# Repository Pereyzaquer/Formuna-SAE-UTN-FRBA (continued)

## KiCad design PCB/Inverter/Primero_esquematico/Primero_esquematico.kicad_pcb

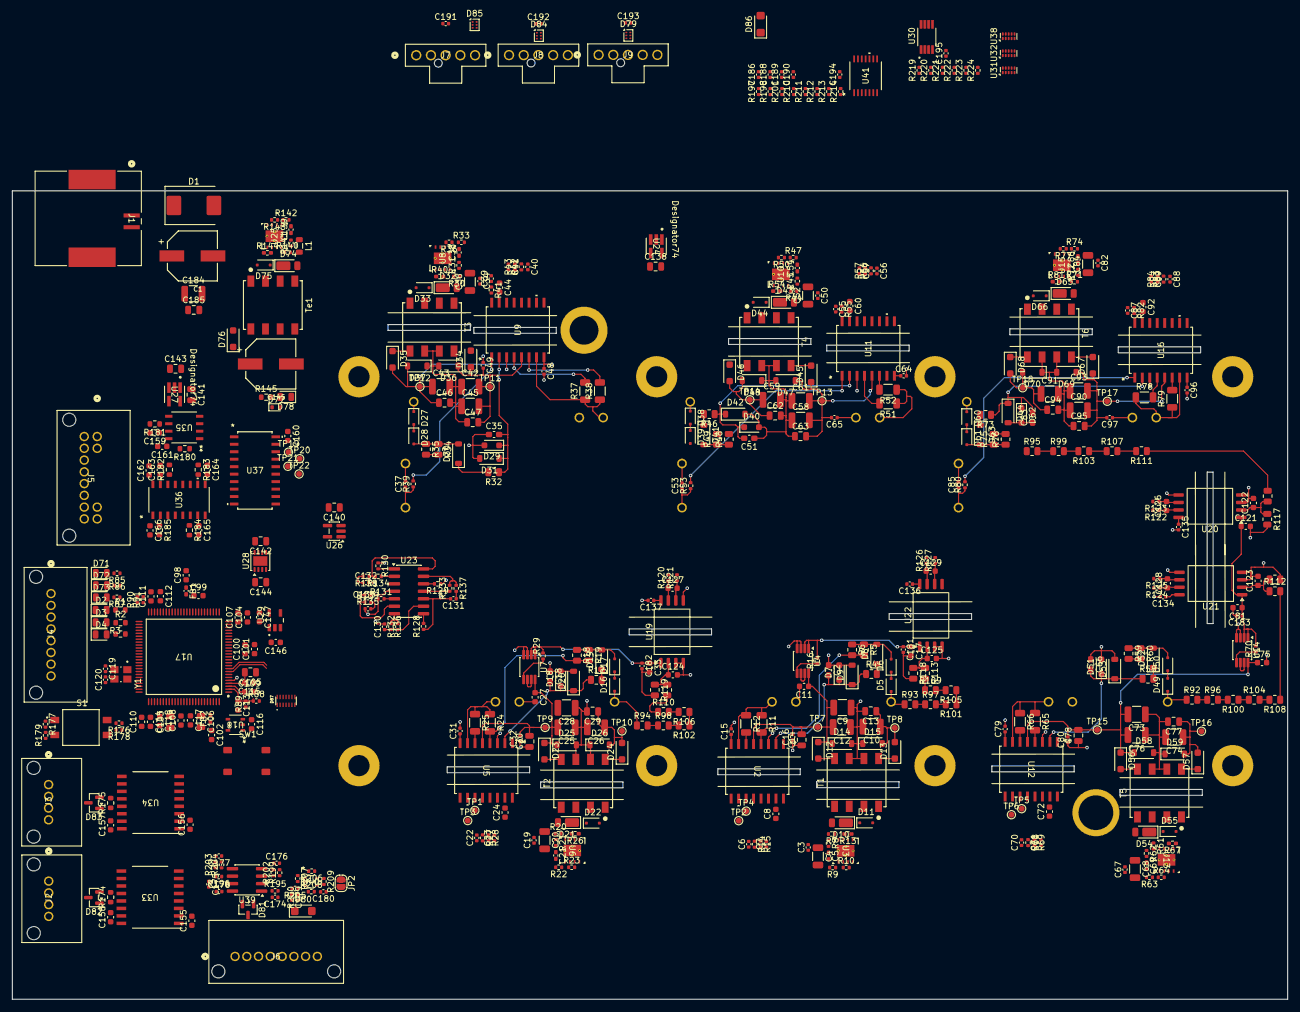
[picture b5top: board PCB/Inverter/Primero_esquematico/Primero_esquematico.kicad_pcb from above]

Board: 6 copper layers, 216.8 x 137.4 mm, 536 parts (1 on the bottom side), 303 nets.

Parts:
C1, C145: 220uF; WCAP-PSLC_8X11.7_DXL_
C2, C18, C35, C51, C66, C83: 56pF; C_0603_1608Metric_Pad1.08x0.95mm_HandSolder
C3, C15, C16, C19, C31, C32, C34, C48, C49, C50, C64, C65, C67, C79, C80, C82, C96, C97, C134, C135, C136, C137, C178, C180, C181, C182, C183, C186, C188, C189, C190: 100nF; C_0402_1005Metric
C4, C20, C36, C52, C68, C84: 10 uF; C_1206_3216Metric
C5, C21, C38, C54, C69, C86, C139: 47nF; C_0402_1005Metric_Pad0.74x0.62mm_HandSolder
C6, C7, C22, C23, C40, C41, C56, C57, C70, C71, C88, C89: 100pF; C_0402_1005Metric
C8, C24, C44, C60, C72, C92, C121: 1uF; C_0603_1608Metric
C9, C12, C25, C28, C42, C45, C58, C61, C73, C76, C90, C93: 10uF; C_1210_3225Metric
C10, C26, C43, C59, C74, C91, C184: 22uF; C_1210_3225Metric
C11, C17, C27, C33, C75, C81: 4.8uF; C_0603_1608Metric
C13, C14, C29, C30, C46, C47, C62, C63, C77, C78, C94, C95, C140, C142, C143, C144: 1uF; C_0805_2012Metric
C37, C53, C85, C119, C120: 10pF; C_0402_1005Metric
C39, C55, C87: 220nF; C_0402_1005Metric
C98, C99, C100, C101, C104, C107: 2.2uF; C_0603_1608Metric
C102: 10uF; C_0603_1608Metric
C103, C105, C106, C138, C141: 10uF; C_0805_2012Metric
C108, C109, C110, C111, C112, C113, C114, C115, C116, C117, C118, C155, C156, C157, C158, C160, C161, C162: 100nF; C_0603_1608Metric
C122, C123, C124, C125, C126, C127, C128, C129: 1nF; C_0603_1608Metric
C130, C131, C132, C133, C174, C175, C195: 1nF; C_0402_1005Metric
C146, C147: 0,1uF; C_0603_1608Metric
C159, C163, C164, C165, C166: 10nF; C_0603_1608Metric
C176, C177, C179: 2.2nF; C_0402_1005Metric
C185: 100nF; C_0805_2012Metric
C191, C192, C193: 47nF; C_0402_1005Metric
C194: 1uF; C_0402_1005Metric
D1: SMDJ13A; D_SMC
D2, D3, D4, D71, D72, D73, D78: APT2012EC; LED_0805_2012Metric
D5, D6, D16, D17, D27, D28, D38, D39, D49, D50, D60, D61: STTH112A; D_SOD-323F
D7, D18, D29, D40, D51, D62: BAT54WS-7-F; D_SOD-323_HandSoldering
D8, D19, D30, D41, D52, D63: BZT52C2V7-TP; D_SOD-123
D9, D20, D31, D42, D53, D64: MMSZ5242B-7-F; D_SOD-123
D10, D21, D32, D43, D54, D65, D74: DFLZ24Q-7; D_PowerDI-123
D11, D22, D33, D44, D55, D66, D75: 1N4148WS-Q; D_SOD-323F
D12, D13, D23, D24, D34, D35, D45, D46, D56, D57, D67, D68, D76: SDM1U100S1F-7; D_SOD-123F
D14, D25, D36, D47, D58, D69: BZT52C18-7-F; D_SOD-123
D15, D26, D37, D48, D59, D70: BZT52B8V2-E3-08; D_SOD-123
D77: SZMM5Z5V6T1G; D_SOD-523
D79, D84, D85: PESD3V3L4UF; SOT-886
D80, D86: SMF16A; D_SMF
D81, D82, D83: PESD5V0S2UAT,215; SOT-23
D87: TPD6E05U06RVZR; SON50P135X350X55-14N
FB1: 60 Ohm; L_0402_1005Metric_Pad0.77x0.64mm_HandSolder
FB2: 220 Ohms; L_0402_1005Metric_Pad0.77x0.64mm_HandSolder
J1: 349128022; CONN_SD-34912-001_02_MOL
J2, J3: 347920040; CONN04_34792_MOL
J4, J6: 347928082; CONN08_34792_MOL
J5: 348250125; CONN_SD-34825-001_12_MOL
J7, J8, J9: 1053091205; CONN_SD-105309-100_05_MOL
JP2: solotest; SolderJumper-2_P1.3mm_Open_RoundedPad1.0x1.5mm
L1: MLZ2012N6R8LT000; L_0805_2012Metric
R1, R2, R3: 2k2; R_0603_1608Metric
R4, R17, R32, R46, R58, R73: 475; R_0805_2012Metric
R5, R6, R18, R19, R34, R35, R48, R49, R59, R60, R75, R76: 2k; R_0805_2012Metric
R7, R20, R30, R44, R61, R71, R140: 246k; R_0402_1005Metric
R8, R21, R31, R45, R62, R72, R141: 37k; R_0402_1005Metric
R9, R22, R33, R47, R63, R74, R142: 12k1; R_0402_1005Metric
R10, R23, R36, R50, R64, R77, R143: 110k; R_0402_1005Metric
R11, R24, R37, R51, R65, R78: 2.4; R_1206_3216Metric
R12, R25, R38, R52, R66, R79: 5.1; R_1206_3216Metric
R13, R26, R40, R54, R67, R81: 154k; R_0402_1005Metric_Pad0.72x0.64mm_HandSolder
R14, R27, R42, R56, R68, R83, R220, R224: 5k; R_0402_1005Metric
R15, R28, R43, R57, R69, R84: 2k; R_0402_1005Metric
R16, R29, R70: 330k; R_0402_1005Metric
R39, R53, R80: 10; R_0402_1005Metric
R41, R55, R82: 360; R_0402_1005Metric
R85, R86, R87: 1k5; R_0402_1005Metric
R88, R90, R91, R177, R179: 0; R_0402_1005Metric
R89, R176, R178, R210, R211, R212, R213, R223: 10k; R_0402_1005Metric
R92, R93, R94, R95, R96, R97, R98, R99, R100, R101, R102, R103, R104, R105, R106, R107, R108, R109, R110, R111, R112, R113, R114, R115: 100k; R_0805_2012Metric
R116, R117, R118, R119: 2k2; R_0805_2012Metric
R120, R121, R122, R123, R124, R125, R126, R127: 4k42; R_0402_1005Metric
R128, R129, R130, R131, R132, R133, R134, R135: 7k68; R_0402_1005Metric
R136, R137, R138, R139, R195, R196: 100; R_0402_1005Metric
R144: 158k; R_0402_1005Metric_Pad0.72x0.64mm_HandSolder
R145: 1k5; R_0603_1608Metric
R174, R175, R181, R182, R183, R184, R185: 120; R_0603_1608Metric
R180: 10k; R_0603_1608Metric
R197, R198, R201: 820; R_0402_1005Metric
R199, R200, R203: 220k; R_0402_1005Metric
R202, R204, R205: 470k; R_0402_1005Metric
R206: 62k; R_0402_1005Metric
R207: 47k; R_0402_1005Metric
R208: 100k; R_0402_1005Metric
R209, R214: 1k; R_0402_1005Metric
R219: 39; R_0402_1005Metric
R221: 20k; R_0402_1005Metric
R222: 11k; R_0402_1005Metric
S1: DS04-254-2-02BK-SMT-TR; SW_DS04-254-2-02BK-SMT-TR
SW1: IT-1187-160GM-G
T1, T2, T3, T4, T5, T6: 750317595; WE-FLYTI_EP7_4436
TP1, TP2, TP3, TP4, TP5, TP6, TP7, TP8, TP9, TP10, TP11, TP12, TP13, TP14, TP15, TP16, TP17, TP18, TP19, TP20, TP21, TP22: TestPoint; TestPoint_Pad_D1.0mm
Te1: Trafo 30uH - 3:1; WE-FLYTI_EP7_4436
U1: FS950R08A6P2BBPSA1; IC_FS950R08A6P2BBPSA1
U2, U5, U9, U11, U12, U16: UCC21750QDWRQ1; SOIC16_DW_TEX-L
U3, U6, U8, U10, U13, U15, U25: LM25180QNGURQ1; NGU0008C
U4, U7, U14: LP2951-5.0_VSSOP; VSSOP-8_3x3mm_P0.65mm
U17: F280049CPZS; PZ0100A_L
U18: TPS3823-33DBVR; DBV5-L
U19, U20, U21, U22: AMC1311BQDWVRQ1; SOIC-8_7.5x5.85mm_P1.27mm
U23: TLV9004QDRQ1; SOIC-14_3.9x8.7mm_P1.27mm
U24, U27: TPS7A2050PDBVR; DBV0005A-IPC_A
U26: LP5907QMFX-3.3Q1; SC-74A-5_1.55x2.9mm_P0.95mm
U28: TLV76733QWDRBRQ1; VSON-8-1EP_3x3mm_P0.65mm_EP1.65x2.4mm
U29: REF2030-Q1; SOT95P0280X110-5N
U30: TLV1702AQDGKRQ1; SOP65P490X110-8N
U31, U32, U38: TPD4E05U06DQA; USON-10_2.5x1.0mm_P0.5mm
U33, U34: ISO1042DWR; DW0016B_HV
U35: SN65HVD82DR; D8_TEX-L
U36: AM26LS32AIDR; D16-L
U37: SN74LVC245ANSR; NS20-L
U39: OPA2196xD; SOIC-8_3.9x4.9mm_P1.27mm
U40: TLV1701AQDCKRQ1; SOIC_DCKRQ1_TEX-L
U41: OPA4991QPWRQ1; TSSOP_PWRQ1_TEX-L
Y1: ABM8GAIG-20.000MHZ-8-7Z-T3; XTAL_ABM8GAIG-20.000MHZ-8-7Z-T3

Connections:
+1V5: R214.1, U29.1 (VBIAS)
+3.3V_analog: C134.1, C135.1, C136.1, C137.1, C140.2, C178.2, C186.2, C191.1, C192.1, C193.1, D79.1 (K1), D84.1 (K1), D85.1 (K1), J7.1, J8.1, J9.1, JP2.1 (A), R206.1, R209.1, R213.1, R224.1, U19.8 (VDD2), U20.8 (VDD2), U21.8 (VDD2), U22.8 (VDD2), U23.3 (V+), U26.5 (OUT), U30.8 (VCC), U39.8 (V+), U40.5 (V+), U41.4 (V+)
+3.3_digital: C8.2, C24.2, C44.2, C60.2, C72.2, C92.2, C98.1, C102.1, C116.1, C144.2, C155.1, C156.1, C160.1, D87.14 (D1P), FB1.1, FB2.1, J4.1, R1.2, R2.2, R3.2, R14.2, R15.2, R27.2, R28.2, R42.2, R43.2, R56.2, R57.2, R68.2, R69.2, R83.2, R84.2, R89.1, R176.1, R178.1, U2.15 (VCC), U5.15 (VCC), U9.15 (VCC), U11.15 (VCC), U12.15 (VCC), U16.15 (VCC), U18.3 (*MR), U18.5 (VDD), U28.1 (OUT), U28.3 (SNS), U33.1 (VCC1), U34.1 (VCC1), U37.1 (DIR), U37.20 (VCC)
+3V0: C104.1, C107.1, C147.1, R220.1, R222.1, U17.24 (VREFHIB_VREFHIC), U17.25 (VREFHIA), U29.5 (VREF)
+5V_Can_1: C158.1, J2.4, U33.11 (VCC2), U33.16 (VCC2)
+5V_Can_2: C157.1, J3.4, U34.11 (VCC2), U34.16 (VCC2)
+5V_analog: C138.2, D86.1 (A1), J6.1, J6.2, U24.5 (OUT)
+5V_digital: C141.2, C146.1, C161.1, C162.1, J5.5, R180.2, U27.5 (OUT), U29.3 (EN), U29.4 (VIN), U32.4 (D2+), U32.5 (D2-), U35.8 (VCC), U36.4 (G), U36.16 (VCC)
+12V: C1.1, C3.2, C4.1, C19.2, C20.1, C34.2, C36.1, C50.2, C52.1, C67.2, C68.1, C82.2, C84.1, C184.1, C185.1, D1.1 (A1), D10.2 (A), D21.2 (A), D32.2 (A), D43.2 (A), D54.2 (A), D65.2 (A), J1.1, L1.1, R7.1, R20.1, R30.1, R44.1, R61.1, R71.1, T1.4, T2.4, T3.4, T4.4, T5.4, T6.4, U3.3 (VIN), U6.3 (VIN), U8.3 (VIN), U10.3 (VIN), U13.3 (VIN), U15.3 (VIN)
/pcb_logica/A: TP19.1 (1_1), U17.93 (GPIO10), U37.18 (B1)
/pcb_logica/B: TP20.1 (1_1), U17.52 (GPIO11), U37.17 (B2)
/pcb_logica/Boot_Mode_1: R178.2, S1.2B, U17.64 (GPIO32)
/pcb_logica/Boot_Mode_2: R176.2, S1.1B, U17.56 (GPIO24)
/pcb_logica/CAN_RX_A: U17.98 (GPIO30), U33.5 (RXD)
/pcb_logica/CAN_RX_B: U17.50 (GPIO13), U34.5 (RXD)
/pcb_logica/CAN_TX_A: U17.99 (GPIO31), U33.3 (TXD)
/pcb_logica/CAN_TX_B: U17.51 (GPIO12), U34.3 (TXD)
/pcb_logica/Clk: U17.74 (GPIO08), U35.4 (D)
/pcb_logica/Current_A: C190.1, R201.2, U17.23 (A0_B15_C15_DACA_OUT)
/pcb_logica/Current_B: C189.1, R198.2, U17.41 (B0)
/pcb_logica/Current_C: C188.1, R197.2, U17.19 (C0)
/pcb_logica/Data: TP22.1 (1_1), U17.84 (GPIO07), U37.15 (B4)
/pcb_logica/ErrorDC: R91.2, R224.2, U30.1 (1OUT), U30.7 (2OUT)
/pcb_logica/F280049C/GPIO18_X2: C119.1, U17.68 (GPIO18_X2), Y1.1
/pcb_logica/F280049C/GP_25_LED_A: R85.1, U17.57 (GPIO25)
/pcb_logica/F280049C/GP_26_LED_B: R86.1, U17.58 (GPIO26)
/pcb_logica/F280049C/GP_27_LED_C: R87.1, U17.59 (GPIO27)
/pcb_logica/F280049C/GP_59_WD: U17.92 (GPIO59), U18.4 (WDI)
/pcb_logica/F280049C/X1: C120.1, U17.69 (X1), Y1.3
/pcb_logica/GD_FLT: C7.2, C23.2, C41.2, C57.2, C71.2, C89.2, D2.2 (A), R1.1, R15.1, R28.1, R43.1, R57.1, R69.1, R84.1, U2.13 (*FLT), U5.13 (*FLT), U9.13 (*FLT), U11.13 (*FLT), U12.13 (*FLT), U16.13 (*FLT), U17.65 (GPIO56)
/pcb_logica/GD_RDY: C6.2, C22.2, C40.2, C56.2, C70.2, C88.2, D3.2 (A), R2.1, R14.1, R27.1, R42.1, R56.1, R68.1, R83.1, U2.12 (RDY), U5.12 (RDY), U9.12 (RDY), U11.12 (RDY), U12.12 (RDY), U16.12 (RDY), U17.66 (GPIO57)
/pcb_logica/LogicSupply/5V_FB: C142.2, C143.2, C145.1, D76.1 (K), D77.1 (K), R145.1, U24.1 (IN), U24.3 (EN), U26.1 (IN), U26.3 (EN), U27.1 (IN), U27.3 (EN), U28.5 (EN), U28.8 (IN)
/pcb_logica/Mcu_reset: C113.1, D87.13 (D1N), J4.2, R88.1, R89.2, U17.2 (XRS_N), U18.1 (*RESET)
/pcb_logica/OCD_OUT: D79.6 (K4), D84.6 (K4), D85.6 (K4), J7.5, J8.5, J9.5, R90.2, R213.2
/pcb_logica/PWM_H_A: TP6.1 (1_1), U12.10 (IN+), U16.11 (IN), U17.79 (GPIO00)
/pcb_logica/PWM_H_B: TP2.1 (1_1), U2.10 (IN+), U17.77 (GPIO02)
/pcb_logica/PWM_H_C: TP3.1 (1_1), U5.10 (IN+), U9.11 (IN), U11.11 (IN), U17.75 (GPIO04)
/pcb_logica/PWM_L_A: TP5.1 (1_1), U12.11 (IN), U16.10 (IN+), U17.78 (GPIO01)
/pcb_logica/PWM_L_B: TP4.1 (1_1), U2.11 (IN), U11.10 (IN+), U17.76 (GPIO03)
/pcb_logica/PWM_L_C: TP1.1 (1_1), U5.11 (IN), U9.10 (IN+), U17.89 (GPIO05)
/pcb_logica/Reset_Pote: C180.2, D4.2 (A), JP2.2 (B), R3.1, R208.2, R209.2, U2.14 (RST/EN), U5.14 (RST/EN), U9.14 (RST/EN), U11.14 (RST/EN), U12.14 (RST/EN), U16.14 (RST/EN), U40.4 (OUT)
/pcb_logica/TCK: D87.9 (D3P), J4.5, U17.60 (TCK)
/pcb_logica/TDI: D87.12 (D2P), J4.3, U17.63 (GPIO35_TDI)
/pcb_logica/TDO: D87.11 (D2N), J4.4, U17.61 (GPIO37_TDO)
/pcb_logica/TMS: D87.8 (D3N), J4.6, U17.62 (TMS)
/pcb_logica/Temp_A: C87.1, R82.1, U17.7 (B2_C6_PGA3_OF)
/pcb_logica/Temp_B: C55.1, R55.1, U17.39 (B4_C8_PGA4_OF)
/pcb_logica/Temp_C: C39.1, R41.1, U17.21 (C2)
/pcb_logica/Tension_A: C132.1, R138.2, U17.10 (A3)
/pcb_logica/Tension_B: C133.1, R139.2, U17.40 (B1_A10_C10_PGA7_OF)
/pcb_logica/Tension_C: C130.1, R136.2, U17.29 (C1)
/pcb_logica/Tension_DC: C131.1, R137.2, R219.1, U17.35 (A5)
/pcb_logica/Z: TP21.1 (1_1), U17.90 (GPIO09), U37.16 (B3)
/pcb_logica/acelerador_1: C174.1, R195.2, U17.9 (A2_B6_PGA1_OF)
/pcb_logica/acelerador_2: C175.1, R196.2, U17.8 (B3_VDAC)
/pcb_logica/apps/opamp_1: C176.2, D81.1 (A1), J6.3, R199.2
/pcb_logica/apps/opamp_2: C177.2, D81.2 (A2), J6.4, R203.2
/pcb_logica/apps/power_ready_conector: R200.2, R205.1, U40.3 (IN-)
/pcb_logica/encoder/A+: J5.4, R185.1, U31.4 (D2+), U36.2 (1A)
/pcb_logica/encoder/A-: C166.1, J5.3, U31.5 (D2-), U36.1 (1B)
/pcb_logica/encoder/A_MCU_5V: U36.3 (1Y), U37.2 (A1)
/pcb_logica/encoder/B+: J5.12, R184.1, U32.2 (D1-), U36.6 (2A)
/pcb_logica/encoder/B-: C165.1, J5.11, U32.1 (D1+), U36.7 (2B)
/pcb_logica/encoder/B_MCU_5V: U36.5 (2Y), U37.3 (A2)
/pcb_logica/encoder/Clock+: J5.1, R181.1, U31.1 (D1+), U35.6 (A)
/pcb_logica/encoder/Clock-: C159.1, J5.2, U31.2 (D1-), U35.7 (B)
/pcb_logica/encoder/DATA_MCU_5V: U36.13 (4Y), U37.5 (A4)
/pcb_logica/encoder/Data+: J5.10, R182.1, U36.14 (4A), U38.2 (D1-)
/pcb_logica/encoder/Data-: C163.1, J5.9, U36.15 (4B), U38.1 (D1+)
/pcb_logica/encoder/Z+: J5.7, R183.1, U36.10 (3A), U38.4 (D2+)
/pcb_logica/encoder/Z-: C164.1, J5.8, U36.9 (3B), U38.5 (D2-)
/pcb_logica/encoder/Z_MCU_5V: U36.11 (3Y), U37.4 (A3)
/pcb_potencia/Gate_Driver/5V_ISO_1: C81.1, C121.1, C183.1, R70.2, U14.1 (OUT), U14.2 (SENSE), U20.1 (VDD1), U21.1 (VDD1)
/pcb_potencia/Gate_Driver/5V_ISO_2: C17.1, C181.1, R16.2, U4.1 (OUT), U4.2 (SENSE), U22.1 (VDD1)
/pcb_potencia/Gate_Driver/5V_ISO_3: C33.1, C182.1, R29.2, U7.1 (OUT), U7.2 (SENSE), U19.1 (VDD1)
/pcb_potencia/Gate_Driver/GD_HS_1/+15V: C90.2, C93.2, C95.2, C97.2, D67.1 (K), D69.1 (K), TP17.1 (1_1), U16.5 (VDD)
/pcb_potencia/Gate_Driver/GD_HS_1/-8V: C91.1, C94.1, C96.1, D68.2 (A), D70.2 (A), TP18.1 (1_1), U16.8 (VEE)
/pcb_potencia/Gate_Driver/GD_HS_1/DESAT: C83.2, D62.1 (K), D64.1 (K), R73.1, U16.2 (DESAT)
/pcb_potencia/Gate_Driver/GD_HS_1/Gate: R78.1, R79.1, U1.G1, U16.7 (CLMPI)
/pcb_potencia/Gate_Driver/GD_HS_1/S_HV: C85.1, R80.1, U1.T1
/pcb_potencia/Gate_Driver/GD_HS_2/+15V: C58.2, C61.2, C63.2, C65.2, D45.1 (K), D47.1 (K), TP13.1 (1_1), U11.5 (VDD)
/pcb_potencia/Gate_Driver/GD_HS_2/-8V: C59.1, C62.1, C64.1, D46.2 (A), D48.2 (A), TP14.1 (1_1), U11.8 (VEE)
/pcb_potencia/Gate_Driver/GD_HS_2/DESAT: C51.2, D40.1 (K), D42.1 (K), R46.1, U11.2 (DESAT)
/pcb_potencia/Gate_Driver/GD_HS_2/Gate: R51.1, R52.1, U1.G3, U11.7 (CLMPI)
/pcb_potencia/Gate_Driver/GD_HS_2/S_HV: C53.1, R53.1, U1.T3
/pcb_potencia/Gate_Driver/GD_HS_3/+15V: C42.2, C45.2, C47.2, C49.2, D34.1 (K), D36.1 (K), TP11.1 (1_1), U9.5 (VDD)
/pcb_potencia/Gate_Driver/GD_HS_3/-8V: C43.1, C46.1, C48.1, D35.2 (A), D37.2 (A), TP12.1 (1_1), U9.8 (VEE)
/pcb_potencia/Gate_Driver/GD_HS_3/DESAT: C35.2, D29.1 (K), D31.1 (K), R32.1, U9.2 (DESAT)
/pcb_potencia/Gate_Driver/GD_HS_3/Gate: R37.1, R38.1, U1.G5, U9.7 (CLMPI)
/pcb_potencia/Gate_Driver/GD_HS_3/S_HV: C37.1, R39.1, U1.T5
/pcb_potencia/Gate_Driver/GD_LS_1/+15V: C73.2, C75.1, C76.2, C78.2, C80.2, D56.1 (K), D58.1 (K), TP15.1 (1_1), U12.5 (VDD), U14.8 (IN)
/pcb_potencia/Gate_Driver/GD_LS_1/-8V: C74.1, C77.1, C79.1, D57.2 (A), D59.2 (A), TP16.1 (1_1), U12.8 (VEE)
/pcb_potencia/Gate_Driver/GD_LS_1/DESAT: C66.2, D51.1 (K), D53.1 (K), R58.1, U12.2 (DESAT)
/pcb_potencia/Gate_Driver/GD_LS_1/Gate: R65.1, R66.1, U1.G2, U12.7 (CLMPI)
/pcb_potencia/Gate_Driver/GD_LS_2/+15V: C9.2, C11.1, C12.2, C14.2, C16.2, D12.1 (K), D14.1 (K), TP7.1 (1_1), U2.5 (VDD), U4.8 (IN)
/pcb_potencia/Gate_Driver/GD_LS_2/-8V: C10.1, C13.1, C15.1, D13.2 (A), D15.2 (A), TP8.1 (1_1), U2.8 (VEE)
/pcb_potencia/Gate_Driver/GD_LS_2/DESAT: C2.2, D7.1 (K), D9.1 (K), R4.1, U2.2 (DESAT)
/pcb_potencia/Gate_Driver/GD_LS_2/Gate: R11.1, R12.1, U1.G4, U2.7 (CLMPI)
/pcb_potencia/Gate_Driver/GD_LS_3/+15V: C25.2, C27.1, C28.2, C30.2, C32.2, D23.1 (K), D25.1 (K), TP9.1 (1_1), U5.5 (VDD), U7.8 (IN)
/pcb_potencia/Gate_Driver/GD_LS_3/-8V: C26.1, C29.1, C31.1, D24.2 (A), D26.2 (A), TP10.1 (1_1), U5.8 (VEE)
/pcb_potencia/Gate_Driver/GD_LS_3/DESAT: C18.2, D18.1 (K), D20.1 (K), R17.1, U5.2 (DESAT)
/pcb_potencia/Gate_Driver/GD_LS_3/Gate: R24.1, R25.1, U1.G6, U5.7 (CLMPI)
/pcb_potencia/Gate_Driver/ISO_GND_HS_1: C83.1, C85.2, C90.1, C91.2, C93.1, C94.2, C95.1, C96.2, C97.1, D62.2 (A), D64.2 (A), D69.2 (A), D70.1 (K), T6.6, T6.7, U1.E1, U1.T2, U16.3 (COM)
/pcb_potencia/Gate_Driver/ISO_GND_HS_2: C51.1, C53.2, C58.1, C59.2, C61.1, C62.2, C63.1, C64.2, C65.1, D40.2 (A), D42.2 (A), D47.2 (A), D48.1 (K), T4.6, T4.7, U1.E3, U1.T4, U11.3 (COM)
/pcb_potencia/Gate_Driver/ISO_GND_HS_3: C35.1, C37.2, C42.1, C43.2, C45.1, C46.2, C47.1, C48.2, C49.1, D29.2 (A), D31.2 (A), D36.2 (A), D37.1 (K), T3.6, T3.7, U1.E5, U1.T6, U9.3 (COM)
/pcb_potencia/Gate_Driver/MP_1: D49.1 (K), R92.1, U1.C2
/pcb_potencia/Gate_Driver/MP_2: D5.1 (K), R93.1, U1.C4
/pcb_potencia/Gate_Driver/MP_3: D16.1 (K), R94.1, U1.C6
/pcb_potencia/Gate_Driver/VCC_DC: D27.1 (K), D38.1 (K), D60.1 (K), R95.1, U1.C1, U1.C3, U1.C5
/pcb_potencia/currentS/U_ref: D79.4 (K3), D84.4 (K3), D85.4 (K3), J7.4, J8.4, J9.4, U41.13 (IN4-), U41.14 (OUT4)
/pcb_potencia/currentS/Uout_1: D85.3 (K2), J7.3, R211.1, U41.3 (IN1+)
/pcb_potencia/currentS/Uout_2: D84.3 (K2), J8.3, R210.1, U41.5 (IN2+)
/pcb_potencia/currentS/Uout_3: D79.3 (K2), J9.3, R212.1, U41.10 (IN3+)
GND: C1.2, C3.1, C4.2, C5.1, C6.1, C7.1, C8.1, C19.1, C20.2, C21.1, C22.1, C23.1, C24.1, C34.1, C36.2, C38.1, C39.2, C40.1, C41.1, C44.1, C50.1, C52.2, C54.1, C55.2, C56.1, C57.1, C60.1, C67.1, C68.2, C69.1, C70.1, C71.1, C72.1, C82.1, C84.2, C86.1, C87.2, C88.1, C89.1, C92.1, C98.2, C99.2, C100.2, C101.2, C102.2, C103.1, C104.2, C105.1, C106.2, C107.2, C108.1, C109.2, C110.1, C111.2, C112.1, C113.2, C114.2, C115.1, C116.2, C117.2, C118.2, C119.2, C120.2, C130.2, C131.2, C132.2, C133.2, C134.2, C135.2, C136.2, C137.2, C138.1, C139.1, C140.1, C141.1, C142.1, C143.1, C144.1, C145.2, C146.2, C147.2, C155.2, C156.2, C160.2, C161.2, C162.2, C174.2, C175.2, C176.1, C177.1, C178.1, C179.1, C180.1, C184.2, C185.2, C186.1, C188.2, C189.2, C190.2, C191.2, C192.2, C193.2, C194.2, C195.1, D1.2 (A2), D2.1 (K), D3.1 (K), D4.1 (K), D71.1 (K), D72.1 (K), D73.1 (K), D77.2 (A), D78.1 (K), D79.2 (A), D79.5 (A), D80.2 (A2), D81.3 (common), D84.2 (A), D84.5 (A), D85.2 (A), D85.5 (A), D86.2 (A2), D87.5 (GND), D87.10 (GND__1), J1.2, J1.MNT1, J1.MNT2, J4.7, J4.8, J5.6, J6.6, J6.7, J6.8, J7.2, J8.2, J9.2, R8.2, R9.2, R21.2, R22.2, R31.2, R33.2, R45.2, R47.2, R62.2, R63.2, R72.2, R74.2, R128.1, R129.1, R130.1, R131.1, R141.2, R142.2, R177.2, R179.2, R202.2, R204.2, R205.2, R207.2, R210.2, R211.2, R212.2, R221.2, R223.2, SW1.1, Te1.5 (SB), Te1.6 (SA), U2.9 (GND), U3.8 (GND), U3.9 (PAD), U5.9 (GND), U6.8 (GND), U6.9 (PAD), U8.8 (GND), U8.9 (PAD), U9.9 (GND), U10.8 (GND), U10.9 (PAD), U11.9 (GND), U12.9 (GND), U13.8 (GND), U13.9 (PAD), U15.8 (GND), U15.9 (PAD), U16.9 (GND), U17.5 (VSS), U17.12 (VSSA), U17.13 (PGA5_GND), U17.14 (PGA1_GND), U17.15 (PGA3_GND), U17.26 (VREFLOB_VREFLOC), U17.27 (VREFLOA), U17.32 (PGA2_GND_PGA4_GND_PGA6_GND), U17.33 (VSSA), U17.42 (PGA7_GND), U17.45 (VSS), U17.72 (VSS), U17.73 (VREGENZ), U17.82 (VSS_SW), U17.86 (VSS), U18.2 (GND), U19.5 (GND2), U20.5 (GND2), U21.5 (GND2), U22.5 (GND2), U23.10 (V-), U24.2 (GND), U25.8 (GND), U25.9 (PAD), U26.2 (GND), U27.2 (GND), U28.4 (GND), U28.6 (GND), U28.9 (PAD), U29.2 (GND), U30.4 (GND), U31.3 (GND), U31.8 (GND), U32.3 (GND), U32.8 (GND), U33.2 (GND1), U33.8 (GND1), U34.2 (GND1), U34.8 (GND1), U35.5 (GND), U36.8 (GND), U36.12 (*G), U37.6 (A5), U37.7 (A6), U37.8 (A7), U37.9 (A8), U37.10 (GND), U37.19 (*OE), U38.3 (GND), U38.8 (GND), U39.4 (V-), U40.2 (V-), U41.11 (V-)
GNDPWR_1: C66.1, C73.1, C74.2, C75.2, C76.1, C77.2, C78.1, C79.2, C80.1, C81.2, C121.2, C122.2, C123.2, C183.2, D51.2 (A), D53.2 (A), D58.2 (A), D59.1 (K), R116.2, R117.2, T5.6, T5.7, U1.E2, U12.3 (COM), U14.3 (SHUTDOWN), U14.4 (GND), U20.3 (VINN), U20.4 (GND1), U21.3 (VINN), U21.4 (GND1)
GNDPWR_2: C2.1, C9.1, C10.2, C11.2, C12.1, C13.2, C14.1, C15.2, C16.1, C17.2, C125.2, C181.2, D7.2 (A), D9.2 (A), D14.2 (A), D15.1 (K), R118.2, T1.6, T1.7, U1.E4, U2.3 (COM), U4.3 (SHUTDOWN), U4.4 (GND), U22.3 (VINN), U22.4 (GND1)
GNDPWR_3: C18.1, C25.1, C26.2, C27.2, C28.1, C29.2, C30.1, C31.2, C32.1, C33.2, C124.2, C182.2, D18.2 (A), D20.2 (A), D25.2 (A), D26.1 (K), R119.2, T2.6, T2.7, U1.E6, U5.3 (COM), U7.3 (SHUTDOWN), U7.4 (GND), U19.3 (VINN), U19.4 (GND1)
GND_Can_1: C158.2, D82.3 (common), J2.3, U33.9 (GND2), U33.10 (GND2), U33.15 (GND2)
GND_Can_2: C157.2, D83.3 (common), J3.3, U34.9 (GND2), U34.10 (GND2), U34.15 (GND2)
unnamed: C99.1, C100.1, C101.1, FB1.2, U17.11 (VDDA), U17.34 (VDDA)
unnamed: C103.2, C105.2, C108.2, C110.2, C112.2, C115.2, U17.4 (VDD), U17.46 (VDD), U17.71 (VDD), U17.87 (VDD)
unnamed: C159.2, R181.2
unnamed: C163.2, R182.2
unnamed: C164.2, R183.2
unnamed: C165.2, R184.2
unnamed: C166.2, R185.2
unnamed: D5.2 (A), D6.1 (K)
unnamed: D6.2 (A), D8.2 (A), R5.1, R6.1
unnamed: D8.1 (K), R4.2
unnamed: D10.1 (K), D11.1 (K)
unnamed: D11.2 (A), R13.1, T1.1, U3.1 (SW)
unnamed: D12.2 (A), T1.5
unnamed: D13.1 (K), T1.8
unnamed: D16.2 (A), D17.1 (K)
unnamed: D17.2 (A), D19.2 (A), R18.1, R19.1
unnamed: D19.1 (K), R17.2
unnamed: D21.1 (K), D22.1 (K)
unnamed: D22.2 (A), R26.1, T2.1, U6.1 (SW)
unnamed: D23.2 (A), T2.5
unnamed: D24.1 (K), T2.8
unnamed: D27.2 (A), D28.1 (K)
unnamed: D28.2 (A), D30.2 (A), R34.1, R35.1
unnamed: D30.1 (K), R32.2
unnamed: D32.1 (K), D33.1 (K)
unnamed: D33.2 (A), R40.1, T3.1, U8.1 (SW)
unnamed: D34.2 (A), T3.5
unnamed: D35.1 (K), T3.8
unnamed: D38.2 (A), D39.1 (K)
unnamed: D39.2 (A), D41.2 (A), R48.1, R49.1
unnamed: D41.1 (K), R46.2
unnamed: D43.1 (K), D44.1 (K)
unnamed: D44.2 (A), R54.1, T4.1, U10.1 (SW)
unnamed: D45.2 (A), T4.5
unnamed: D46.1 (K), T4.8
unnamed: D49.2 (A), D50.1 (K)
unnamed: D50.2 (A), D52.2 (A), R59.1, R60.1
unnamed: D52.1 (K), R58.2
unnamed: D54.1 (K), D55.1 (K)
unnamed: D55.2 (A), R67.1, T5.1, U13.1 (SW)
unnamed: D56.2 (A), T5.5
unnamed: D57.1 (K), T5.8
unnamed: D60.2 (A), D61.1 (K)
unnamed: D61.2 (A), D63.2 (A), R75.1, R76.1
unnamed: D63.1 (K), R73.2
unnamed: D65.1 (K), D66.1 (K)
unnamed: D66.2 (A), R81.1, T6.1, U15.1 (SW)
unnamed: D67.2 (A), T6.5
unnamed: D68.1 (K), T6.8
unnamed: D71.2 (A), R85.2
unnamed: D72.2 (A), R86.2
unnamed: D73.2 (A), R87.2
unnamed: D74.2 (A), L1.2, R140.1, Te1.4 (AB), U25.3 (VIN)
unnamed: D74.1 (K), D75.1 (K)
unnamed: D75.2 (A), R144.1, Te1.1 (AA), U25.1 (SW)
unnamed: D76.2 (A), Te1.7 (SA), Te1.8 (SA)
unnamed: D78.2 (A), R145.2
unnamed: C179.2, D80.1 (A1), J6.5, R200.1
unnamed: D82.1 (A1), J2.2, R174.1, U33.13 (CANH)
unnamed: D82.2 (A2), J2.1, R174.2, U33.12 (CANL)
unnamed: D83.1 (A1), J3.2, R175.1, U34.13 (CANH)
unnamed: D83.2 (A2), J3.1, R175.2, U34.12 (CANL)
unnamed: R88.2, SW1.2
unnamed: R92.2, R96.1
unnamed: R93.2, R97.1
unnamed: R94.2, R98.1
unnamed: R95.2, R99.1
unnamed: R100.1, R104.1
unnamed: R96.2, R100.2
unnamed: R101.1, R105.1
unnamed: R97.2, R101.2
unnamed: R102.1, R106.1
unnamed: R98.2, R102.2
unnamed: R103.1, R107.1
unnamed: R99.2, R103.2
unnamed: R104.2, R108.2
unnamed: R105.2, R109.2
unnamed: R106.2, R110.2
unnamed: R107.2, R111.2
unnamed: R108.1, R112.2
unnamed: R109.1, R113.2
unnamed: R110.1, R114.2
unnamed: R111.1, R115.2
unnamed: R132.2, R136.1, U23.7
unnamed: R133.2, R137.1, U23.13
unnamed: R134.2, R138.1, U23.14
unnamed: R135.2, R139.1, U23.6
unnamed: R177.1, S1.1A
unnamed: R179.1, S1.2A
unnamed: R5.2, R6.2, R11.2, U2.4 (OUTH)
unnamed: R12.2, U2.6 (OUTL)
unnamed: R7.2, R8.1, U3.4 (EN_UVLO)
unnamed: R13.2, U3.2 (FB)
unnamed: R10.2, U3.7 (RSET)
unnamed: C5.2, U3.5 (SS_BIAS)
unnamed: R9.1, R10.1, U3.6 (TC)
unnamed: U4.6 (VTAP), U4.7 (FEEDBACK)
unnamed: R16.1, U4.5 (~ERROR)
unnamed: R18.2, R19.2, R24.2, U5.4 (OUTH)
unnamed: R25.2, U5.6 (OUTL)
unnamed: R20.2, R21.1, U6.4 (EN_UVLO)
unnamed: R26.2, U6.2 (FB)
unnamed: R23.2, U6.7 (RSET)
unnamed: C21.2, U6.5 (SS_BIAS)
unnamed: R22.1, R23.1, U6.6 (TC)
unnamed: U7.6 (VTAP), U7.7 (FEEDBACK)
unnamed: R29.1, U7.5 (~ERROR)
unnamed: R30.2, R31.1, U8.4 (EN_UVLO)
unnamed: R40.2, U8.2 (FB)
unnamed: R36.2, U8.7 (RSET)
unnamed: C38.2, U8.5 (SS_BIAS)
unnamed: R33.1, R36.1, U8.6 (TC)
unnamed: R39.2, U9.1 (AIN)
unnamed: R41.2, U9.16 (APWM)
unnamed: R34.2, R35.2, R37.2, U9.4 (OUTH)
unnamed: R38.2, U9.6 (OUTL)
unnamed: R44.2, R45.1, U10.4 (EN_UVLO)
unnamed: R54.2, U10.2 (FB)
unnamed: R50.2, U10.7 (RSET)
unnamed: C54.2, U10.5 (SS_BIAS)
unnamed: R47.1, R50.1, U10.6 (TC)
unnamed: R53.2, U11.1 (AIN)
unnamed: R55.2, U11.16 (APWM)
unnamed: R48.2, R49.2, R51.2, U11.4 (OUTH)
unnamed: R52.2, U11.6 (OUTL)
unnamed: R59.2, R60.2, R65.2, U12.4 (OUTH)
unnamed: R66.2, U12.6 (OUTL)
unnamed: R61.2, R62.1, U13.4 (EN_UVLO)
unnamed: R67.2, U13.2 (FB)
unnamed: R64.2, U13.7 (RSET)
unnamed: C69.2, U13.5 (SS_BIAS)
unnamed: R63.1, R64.1, U13.6 (TC)
unnamed: U14.6 (VTAP), U14.7 (FEEDBACK)
unnamed: R70.1, U14.5 (~ERROR)
unnamed: R71.2, R72.1, U15.4 (EN_UVLO)
unnamed: R81.2, U15.2 (FB)
unnamed: R77.2, U15.7 (RSET)
unnamed: C86.2, U15.5 (SS_BIAS)
unnamed: R74.1, R77.1, U15.6 (TC)
unnamed: R80.2, U16.1 (AIN)
unnamed: R82.2, U16.16 (APWM)
unnamed: R75.2, R76.2, R78.2, U16.4 (OUTH)
unnamed: R79.2, U16.6 (OUTL)
unnamed: R90.1, U17.49 (FLT1)
unnamed: R91.1, U17.48 (FLT2)
unnamed: C106.1, C109.1, C111.1, C114.1, C117.1, C118.1, FB2.2, U17.3 (VDDIO), U17.47 (VDDIO), U17.70 (VDDIO), U17.80 (VDDIO_SW), U17.88 (VDDIO)
unnamed: C124.1, R114.1, R119.1, U19.2 (VINP)
unnamed: C127.2, R121.1, U19.6 (VOUTN)
unnamed: C127.1, R120.1, U19.7 (VOUTP)
unnamed: C122.1, R115.1, R117.1, U20.2 (VINP)
unnamed: C126.2, R123.1, U20.6 (VOUTN)
unnamed: C126.1, R122.1, U20.7 (VOUTP)
unnamed: C123.1, R112.1, R116.1, U21.2 (VINP)
unnamed: C128.2, R125.1, U21.6 (VOUTN)
unnamed: C128.1, R124.1, U21.7 (VOUTP)
unnamed: C125.1, R113.1, R118.1, U22.2 (VINP)
unnamed: C129.2, R127.1, U22.6 (VOUTN)
unnamed: C129.1, R126.1, U22.7 (VOUTP)
unnamed: R124.2, R134.1, U23.2 (+)
unnamed: R125.2, R130.2, U23.1 (-)
unnamed: R126.2, R135.1, U23.4 (+)
unnamed: R127.2, R131.2, U23.5 (-)
unnamed: R120.2, R132.1, U23.9 (+)
unnamed: R121.2, R128.2, U23.8 (-)
unnamed: R122.2, R133.1, U23.11 (+)
unnamed: R123.2, R129.2, U23.12 (-)
unnamed: R140.2, R141.1, U25.4 (EN_UVLO)
unnamed: R144.2, U25.2 (FB)
unnamed: R143.2, U25.7 (RSET)
unnamed: C139.2, U25.5 (SS_BIAS)
unnamed: R142.1, R143.1, U25.6 (TC)
unnamed: R220.2, R221.1, U30.3 (1IN+)
unnamed: C195.2, R219.2, U30.2 (1IN-), U30.5 (2IN+)
unnamed: R222.2, R223.1, U30.6 (2IN-)
unnamed: R180.1, U35.2 (*RE), U35.3 (DE)
unnamed: R199.1, R202.1, U39.3 (+)
unnamed: R195.1, U39.1, U39.2 (-)
unnamed: R203.1, R204.1, U39.5 (+)
unnamed: R196.1, U39.6 (-), U39.7
unnamed: R206.2, R207.1, R208.1, U40.1 (IN+)
unnamed: R197.1, U41.1 (OUT1), U41.2 (IN1-)
unnamed: R198.1, U41.6 (IN2-), U41.7 (OUT2)
unnamed: R201.1, U41.8 (OUT3), U41.9 (IN3-)
unnamed: C194.1, R214.2, U41.12 (IN4+)

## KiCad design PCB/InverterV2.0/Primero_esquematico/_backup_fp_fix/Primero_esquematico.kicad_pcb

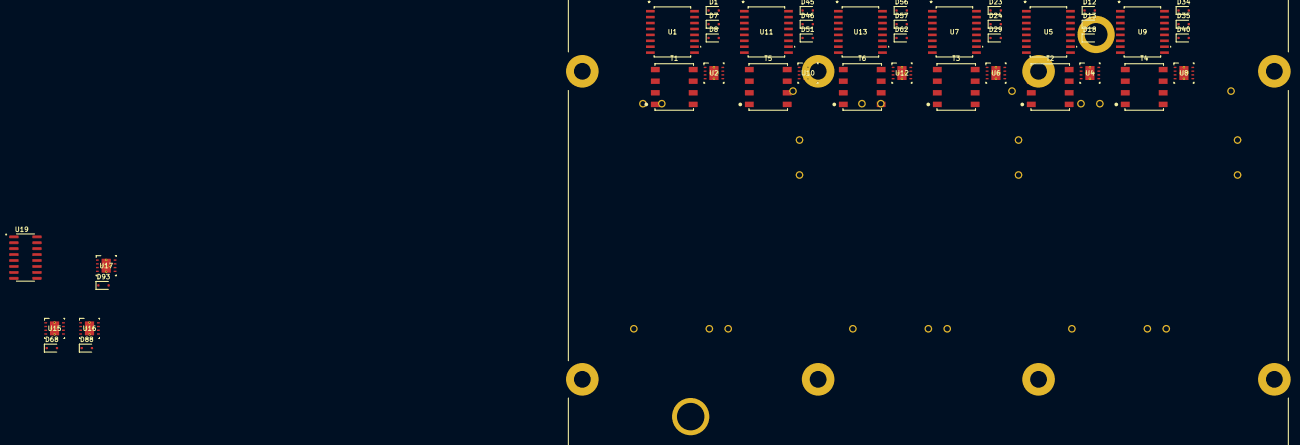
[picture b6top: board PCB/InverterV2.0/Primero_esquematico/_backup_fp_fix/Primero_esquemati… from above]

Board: 2 copper layers, 44 parts (0 on the bottom side), 46 nets, no tracks yet.

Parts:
D1, D18, D29, D40, D51, D62, D68, D88, D93: 1N4148WS-Q; D_SOD-323F
D7, D8, D12, D13, D23, D24, D34, D35, D45, D46, D56, D57: STTH112A; D_SOD-323F
T1, T2, T3, T4, T5, T6: 750317595; WE-FLYTI_EP7_4436
U1, U5, U7, U9, U11, U13: UCC21750QDWRQ1; SOIC16_DW_TEX
U2, U4, U6, U8, U10, U12, U15, U16, U17: LM25180QNGURQ1; NGU0008C
U3: FS950R08A6P2BBPSA1; IC_FS950R08A6P2BBPSA1
U19: AM26C32IDR; SOIC127P600X175-16N

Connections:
/Gate_Driver/3,3V: U1.15 (VCC), U5.15 (VCC), U7.15 (VCC), U9.15 (VCC), U11.15 (VCC), U13.15 (VCC)
/Gate_Driver/15V: T1.1, T2.1, T3.1, T4.1, T5.1, T6.1, U2.3 (VIN), U4.3 (VIN), U6.3 (VIN), U8.3 (VIN), U10.3 (VIN), U12.3 (VIN), U15.3 (VIN)
/Gate_Driver/C1_In_neg: U1.10 (IN+), U13.11 (IN)
/Gate_Driver/C1_In_pos: U1.11 (IN), U13.10 (IN+)
/Gate_Driver/C2_In_neg: U5.10 (IN+), U11.11 (IN)
/Gate_Driver/C3_In_neg: U7.10 (IN+), U9.11 (IN)
/Gate_Driver/C3_In_pos: U5.11 (IN), U7.11 (IN), U9.10 (IN+)
/Gate_Driver/GDsupply1/Colector: D12.1 (K), U3.C3
/Gate_Driver/GDsupply1/Gate: U3.G3, U5.7 (CLMPI)
/Gate_Driver/GDsupply1/ISO_GND: T2.6, T2.7, U3.T4, U5.3 (COM), U5.4 (OUTH)
/Gate_Driver/GDsupply2/Colector: D23.1 (K), U3.C5
/Gate_Driver/GDsupply2/Gate: U3.G5, U7.7 (CLMPI)
/Gate_Driver/GDsupply2/ISO_GND: T3.6, T3.7, U3.T6, U7.3 (COM), U7.4 (OUTH)
/Gate_Driver/GDsupply3/Colector: D34.1 (K), U3.C6
/Gate_Driver/GDsupply3/Gate: U3.G6, U9.7 (CLMPI)
/Gate_Driver/GDsupply3/ISO_GND: T4.6, T4.7, U9.3 (COM), U9.4 (OUTH)
/Gate_Driver/GDsupply4/Colector: D45.1 (K), U3.C4
/Gate_Driver/GDsupply4/Gate: U3.G4, U11.7 (CLMPI)
/Gate_Driver/GDsupply4/ISO_GND: T5.6, T5.7, U11.3 (COM), U11.4 (OUTH)
/Gate_Driver/GDsupply5/Colector: D56.1 (K), U3.C2
/Gate_Driver/GDsupply5/Gate: U3.G2, U13.7 (CLMPI)
/Gate_Driver/GDsupply5/ISO_GND: T6.6, T6.7, U13.3 (COM), U13.4 (OUTH)
/Gate_Driver/GDsupply/Colector: D7.1 (K), U3.C1
/Gate_Driver/GDsupply/Gate: U1.7 (CLMPI), U3.G1
/Gate_Driver/GDsupply/ISO_GND: T1.6, T1.7, U1.3 (COM), U1.4 (OUTH), U3.T2
/Gate_Driver/GND_DC: U3.E1, U3.E3, U3.E5
/Gate_Driver/RDY: U1.12 (RDY), U5.12 (RDY), U7.12 (RDY), U9.12 (RDY), U11.12 (RDY), U13.12 (RDY)
/Gate_Driver/Reset: U1.14 (RST/EN), U5.14 (RST/EN), U7.14 (RST/EN), U9.14 (RST/EN), U11.14 (RST/EN), U13.14 (RST/EN)
/Gate_Driver/VCC_DC: U3.E2, U3.E4, U3.E6
/Gate_Driver/~FLT: U1.13 (*FLT), U5.13 (*FLT), U7.13 (*FLT), U9.13 (*FLT), U11.13 (*FLT), U13.13 (*FLT)
GND: U1.9 (GND), U2.8 (GND), U2.9 (PAD), U4.8 (GND), U4.9 (PAD), U5.9 (GND), U6.8 (GND), U6.9 (PAD), U7.9 (GND), U8.8 (GND), U8.9 (PAD), U9.9 (GND), U10.8 (GND), U10.9 (PAD), U11.9 (GND), U12.8 (GND), U12.9 (PAD), U13.9 (GND), U15.8 (GND), U15.9 (PAD), U16.8 (GND), U16.9 (PAD), U17.8 (GND), U17.9 (PAD)
unnamed: D1.2 (A), T1.4, U2.1 (SW)
unnamed: D7.2 (A), D8.1 (K)
unnamed: D12.2 (A), D13.1 (K)
unnamed: D18.2 (A), T2.4, U4.1 (SW)
unnamed: D23.2 (A), D24.1 (K)
unnamed: D29.2 (A), T3.4, U6.1 (SW)
unnamed: D34.2 (A), D35.1 (K)
unnamed: D40.2 (A), T4.4, U8.1 (SW)
unnamed: D45.2 (A), D46.1 (K)
unnamed: D51.2 (A), T5.4, U10.1 (SW)
unnamed: D56.2 (A), D57.1 (K)
unnamed: D62.2 (A), T6.4, U12.1 (SW)
unnamed: D68.2 (A), U15.1 (SW)
unnamed: D88.2 (A), U16.1 (SW)
unnamed: D93.2 (A), U17.1 (SW)
